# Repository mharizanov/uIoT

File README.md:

uIoT
====

Micro Internet of Things gateway, based on Simon K's work

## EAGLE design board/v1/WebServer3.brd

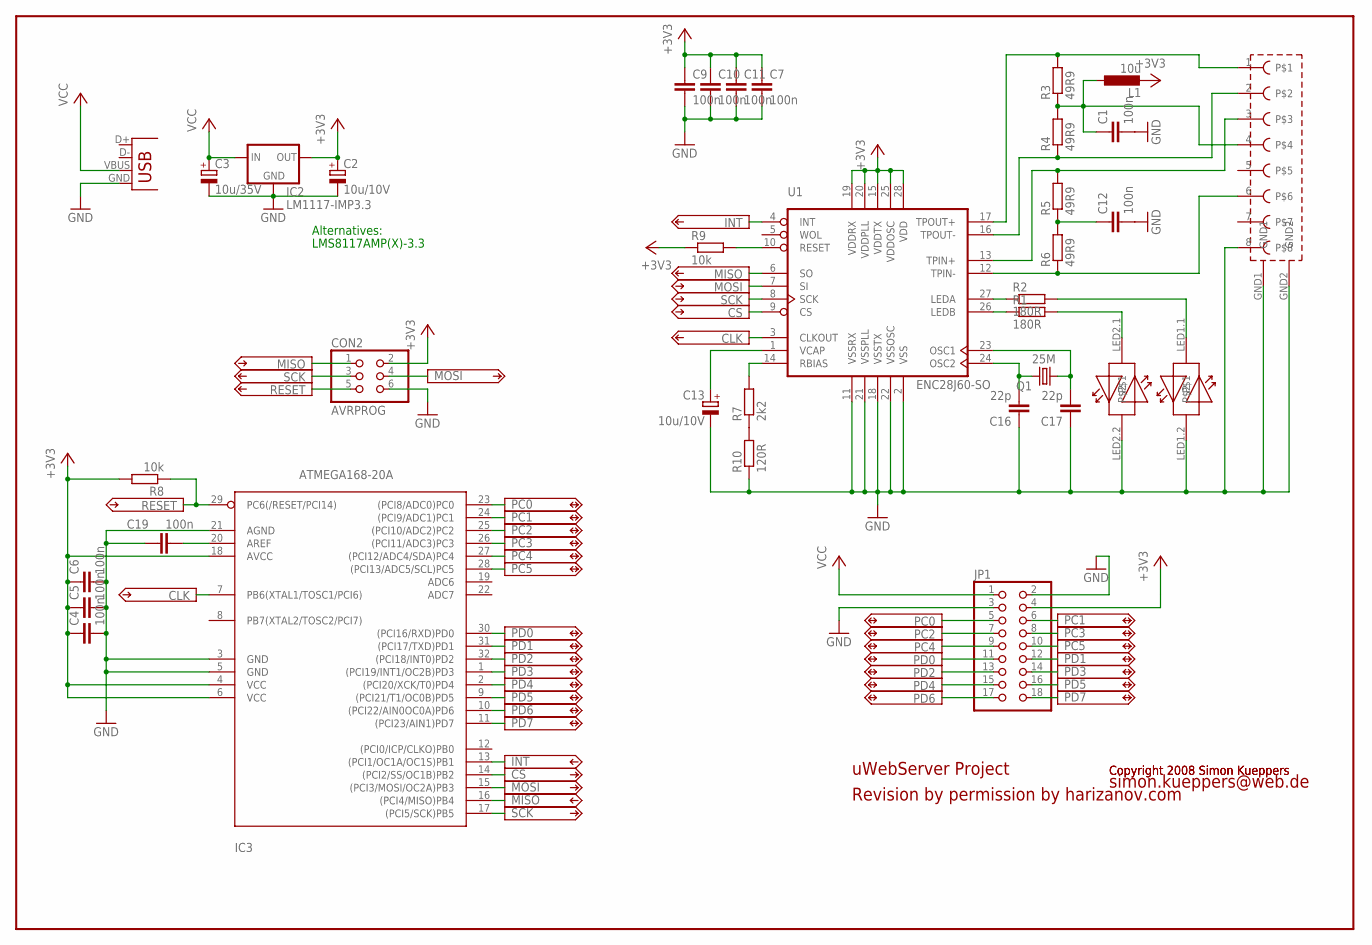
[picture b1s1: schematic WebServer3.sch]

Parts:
C1, C4, C5, C6, C7, C9, C10, C11, C12, C19: 100n; C0805
C2, C13: 10u/10V; SMC_A
C3: 10u/35V; SMC_C
C16, C17: 22p; C0805
CON2: AVRPROG; 2X03
IC2: LM1117-IMP3.3; SOT223
IC3: ATMEGA168-20A; TQFP32-08
JP1: PINHD-2X9; 2X09
L1: 10u; 0207/10
MAGJACK: MAGJACK
Q1: 25M; HC49UP
R1, R2: 180R; R0805
R3, R4, R5, R6: 49R9; R0805
R7: 2k2; R0805
R8, R9: 10k; R0805
R10: 120R; R0805
U1: ENC28J60-SO; SO28W
X1: USB-MICROB

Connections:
+3V3: C2.+, C4.1, C5.1, C6.1, C7.1, C9.1, C10.1, C11.1, CON2.2, IC2.2 (OUT), IC3.4 (VCC), IC3.6 (VCC), IC3.18 (AVCC), JP1.4, L1.2, R8.2, R9.1, U1.15 (VDDTX), U1.19 (VDDRX), U1.20 (VDDPLL), U1.25 (VDDOSC), U1.28 (VDD)
CLK: IC3.7 (PB6(XTAL1/TOSC1/PCI6)), U1.3 (CLKOUT)
CS: IC3.14 ((PCI2/SS/OC1B)PB2), U1.9 (CS)
GND: C1.2, C2.-, C3.-, C4.2, C5.2, C6.2, C7.2, C9.2, C10.2, C11.2, C12.2, C13.-, C16.1, C17.1, C19.1, CON2.6, IC2.1 (GND), IC3.3 (GND), IC3.5 (GND), IC3.21 (AGND), JP1.2, JP1.3, MAGJACK.8, MAGJACK.GND1, MAGJACK.GND2, MAGJACK.LED1.2, MAGJACK.LED2.2, R10.1, U1.2 (VSS), U1.11 (VSSRX), U1.18 (VSSTX), U1.21 (VSSPLL), U1.22 (VSSOSC), X1.GND
INT: IC3.13 ((PCI1/OC1A/OC1S)PB1), U1.4 (INT)
MISO: CON2.1, IC3.16 ((PCI4/MISO)PB4), U1.6 (SO)
MOSI: CON2.4, IC3.15 ((PCI3/MOSI/OC2A)PB3), U1.7 (SI)
unnamed: R7.1, R10.2
unnamed: C13.+, U1.1 (VCAP)
unnamed: R7.2, U1.14 (RBIAS)
unnamed: C17.2, Q1.1, U1.23 (OSC1)
unnamed: C16.2, Q1.2, U1.24 (OSC2)
unnamed: R2.1, U1.27 (LEDA)
unnamed: C19.2, IC3.20 (AREF)
unnamed: R1.1, U1.26 (LEDB)
unnamed: MAGJACK.LED1.1, R2.2
unnamed: R9.2, U1.10 (RESET)
unnamed: MAGJACK.LED2.1, R1.2
unnamed: C1.1, L1.1, MAGJACK.4, R3.1, R4.2
unnamed: C12.1, R5.1, R6.2
unnamed: MAGJACK.6, R6.1, U1.12 (TPIN-)
unnamed: MAGJACK.3, R5.2, U1.13 (TPIN+)
unnamed: MAGJACK.2, R4.1, U1.16 (TPOUT-)
unnamed: MAGJACK.1, R3.2, U1.17 (TPOUT+)
PC0: IC3.23 ((PCI8/ADC0)PC0), JP1.5
PC1: IC3.24 ((PCI9/ADC1)PC1), JP1.6
PC2: IC3.25 ((PCI10/ADC2)PC2), JP1.7
PC3: IC3.26 ((PCI11/ADC3)PC3), JP1.8
PC4: IC3.27 ((PCI12/ADC4/SDA)PC4), JP1.9
PC5: IC3.28 ((PCI13/ADC5/SCL)PC5), JP1.10
PD0: IC3.30 ((PCI16/RXD)PD0), JP1.11
PD1: IC3.31 ((PCI17/TXD)PD1), JP1.12
PD2: IC3.32 ((PCI18/INT0)PD2), JP1.13
PD3: IC3.1 ((PCI19/INT1/OC2B)PD3), JP1.14
PD4: IC3.2 ((PCI20/XCK/T0)PD4), JP1.15
PD5: IC3.9 ((PCI21/T1/OC0B)PD5), JP1.16
PD6: IC3.10 ((PCI22/AIN0OC0A)PD6), JP1.17
PD7: IC3.11 ((PCI23/AIN1)PD7), JP1.18
RESET: CON2.5, IC3.29 (PC6(/RESET/PCI14)), R8.1
SCK: CON2.3, IC3.17 ((PCI5/SCK)PB5), U1.8 (SCK)
VCC: C3.+, IC2.3 (IN), JP1.1, X1.VBUS

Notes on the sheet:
Alternatives:
LMS8117AMP(X)-3.3
uWebServer Project
Copyright 2008 Simon Kueppers
simon.kueppers@web.de
Revision by permission by harizanov.com

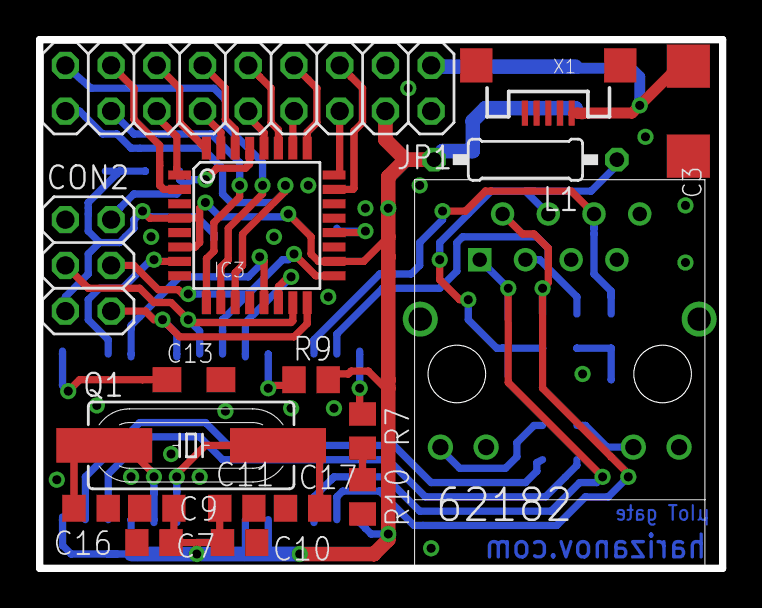
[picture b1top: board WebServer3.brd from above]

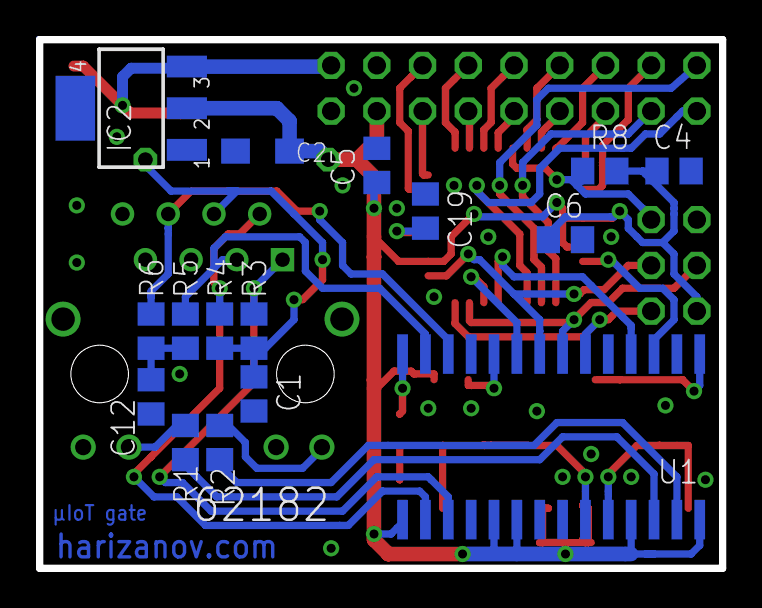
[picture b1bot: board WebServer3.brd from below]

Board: 2 copper layers, 37.9 x 29.4 mm, 34 parts (16 on the bottom side), 41 nets.

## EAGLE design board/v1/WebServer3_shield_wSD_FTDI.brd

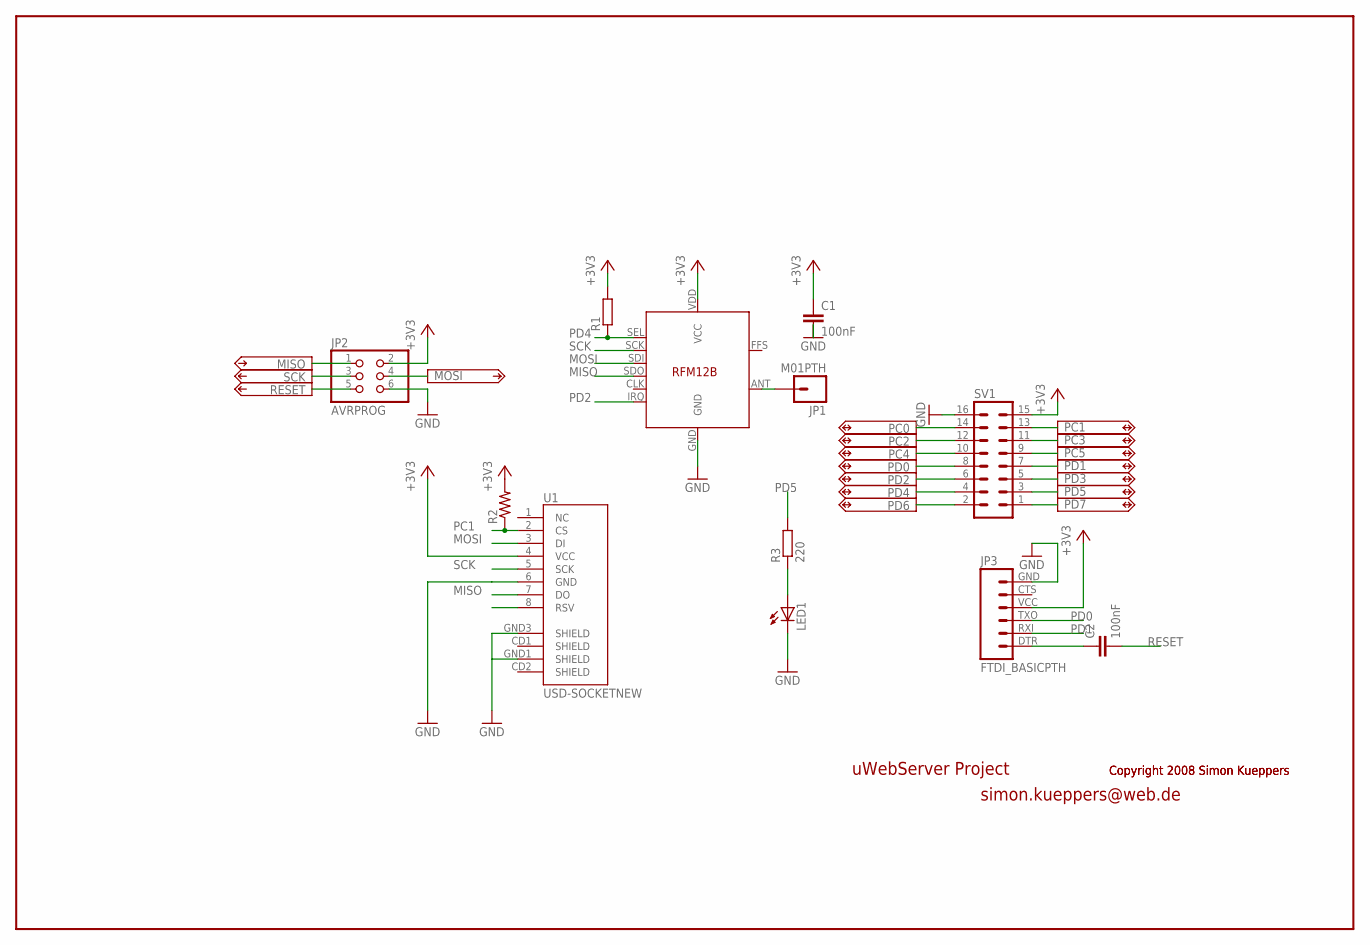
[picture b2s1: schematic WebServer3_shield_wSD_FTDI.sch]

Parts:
C1, C2: 100nF; C0805
JP1: M01PTH; 1X01
JP2: AVRPROG; 2X03
JP3: FTDI_BASICPTH; FTDI_BASIC
LED1: LED0603; LED-0603
R1: R-EU_R0805; R0805
R2: RESISTOR0805-RES; 0805
R3: 220; R0805
RFM12B: RFM12B
SV1: MA08-2
U1: USD-SOCKETNEW; MICRO-SD-SOCKET-PP

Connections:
+3V3: C1.1, JP2.2, JP3.VCC (4), R1.2, R2.2, RFM12B.VDD (VCC), SV1.15, U1.4 (VCC)
GND: C1.2, JP2.6, JP3.GND (6), LED1.C, RFM12B.GND, SV1.16, U1.6 (GND), U1.GND3 (SHIELD)
MISO: JP2.1, RFM12B.SDO, U1.7 (DO)
MOSI: JP2.4, RFM12B.SDI, U1.3 (DI)
unnamed: LED1.A, R3.1
unnamed: JP1.1, RFM12B.ANT
unnamed: C2.1, JP3.DTR (1)
PC0: SV1.14
PC1: R2.1, SV1.13, U1.2 (CS)
PC2: SV1.12
PC3: SV1.11
PC4: SV1.10
PC5: SV1.9
PD0: JP3.TXO (3), SV1.8
PD1: JP3.RXI (2), SV1.7
PD2: RFM12B.IRQ, SV1.6
PD3: SV1.5
PD4: R1.1, RFM12B.SEL, SV1.4
PD5: R3.2, SV1.3
PD6: SV1.2
PD7: SV1.1
RESET: C2.2, JP2.5
SCK: JP2.3, RFM12B.SCK, U1.5 (SCK)

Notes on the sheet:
uWebServer Project
Copyright 2008 Simon Kueppers
simon.kueppers@web.de

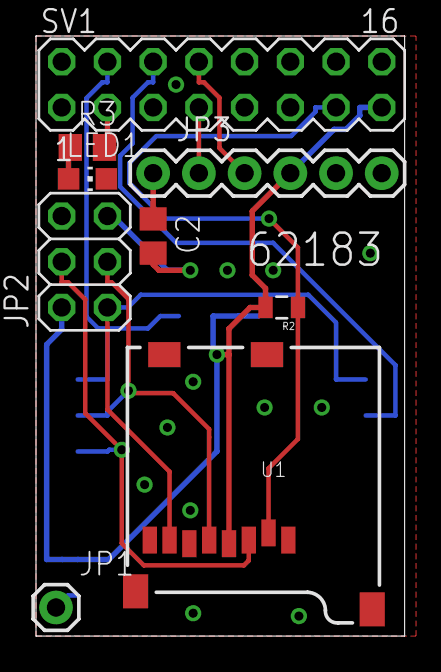
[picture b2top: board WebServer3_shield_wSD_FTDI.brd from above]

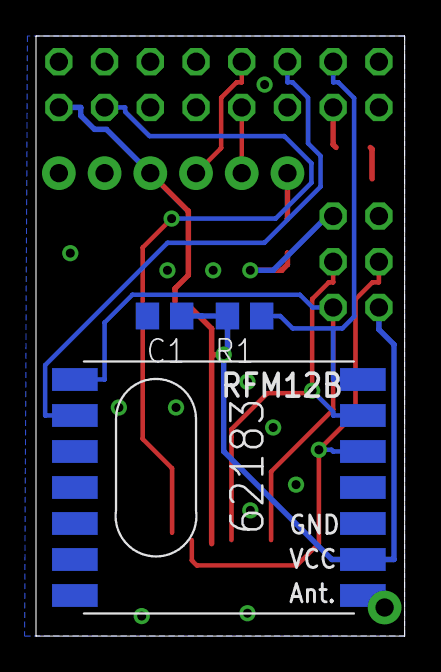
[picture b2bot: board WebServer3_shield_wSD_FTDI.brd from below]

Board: 2 copper layers, 20.5 x 33.3 mm, 12 parts (3 on the bottom side), 15 nets.

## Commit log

2012-12-27 Iitial
2012-12-28 Capture RF12b stream to SD card example
2013-01-21 added more examples
2013-01-24 added bootloaders
2013-05-27 more examples
2013-08-13 emoncms example update
2013-09-03 SD configuration example
2013-09-04 minor updates
2013-09-06 Switched to 'stashes'
2013-09-08 RAM usage optimizations
2013-09-08 sen.se and xively examples
2013-09-08 update the example
2013-09-21 Added polling emoncms funtionality

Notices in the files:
parts and their libraries:
SparkFun: Licensing: CC v3.0 Share-Alike You are welcome to use this library for commercial purposes.
